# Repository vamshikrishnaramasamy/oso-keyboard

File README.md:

# OSO Keyboard

Demo: https://vamshikrishnaramasamy.github.io/oso-keyboard/

Repository/README: https://github.com/vamshikrishnaramasamy/oso-keyboard

OSO Keyboard is an open-source 75% mechanical keyboard project with a custom
ESP32-S3 programmable PCB target, USB/BLE/Wi-Fi firmware plans, and parametric CAD.

Current design target:

- 82-key 75% ANSI layout with a flush hot-swappable OSO module bay
- Onboard ESP32-S3-WROOM-1U module as the main brain
- USB-C
- 10-contact programmable module dock replacing the Esc/F1 corner
- ESP-IDF/TinyUSB wired firmware target, with BLE/Wi-Fi config planned
- MX hotswap switch footprints
- PCB-mounted stabilizers
- Factory-assembled SMD diodes and ESP32-S3 support parts

The project is intentionally source-driven: edit `hardware/layout/oso75.layout.json`,
then run the generator to refresh firmware layout metadata, CAD key positions,
PCB circuit netlists, and the KiCad starting project.

## Quick Start

```sh
npm run generate
npm run validate
```

Generated CAD lives in `hardware/cad/generated/`. The KiCad project lives in
`hardware/kicad/oso75/`.

## Reviewer File Map

PCB source files:

- KiCad project: `hardware/kicad/oso75/oso75.kicad_pro`
- KiCad schematic: `hardware/kicad/oso75/oso75.kicad_sch`
- KiCad PCB: `hardware/kicad/oso75/oso75.kicad_pcb`
- Order-ready Gerbers/BOM/CPL: `hardware/kicad/oso75/fab/`
- Reviewer BOM with purchase links: `hardware/bom.csv`

CAD source and exports:

- Parametric CAD source: `hardware/cad/build123d/oso75_case.py`
- Full assembly render: `hardware/cad/build123d/oso75_preview_exploded.png`
- Full assembly STEP/GLB: `hardware/cad/build123d/oso75_assembly.step` and
  `hardware/cad/build123d/oso75_assembly.glb`
- Split case top: `hardware/cad/build123d/oso75_case_bezel.step/.stl`
- Split case bottom: `hardware/cad/build123d/oso75_case_bottom.step/.stl`
- Switch plate: `hardware/cad/build123d/oso75_plate.step/.stl`
- Module bay cover: `hardware/cad/build123d/oso75_bay_cover.step/.stl`

## Status

This is the first hardware bring-up pass. The layout, firmware skeleton, CAD
plate/case model, ESP32-S3 pin plan, PCB circuit netlists, and KiCad board
starting point are in place.

2026-06-10: a full orientation audit against the proven annovax75 reference
found the PCB was **physically mirrored** (rows y-inverted: a built board would
have had `~` on the right and Enter on the left). The board was y-flipped
(placements mirrored, every footprint rotated 180°, diodes re-seated at the
x-mirrored offset about their switch) and re-routed from scratch. KiCad 10.0.3
reports 0 DRC errors and 0 unconnected items; drill files reconcile exactly.
The CAD model was already correct and is byte-identical across the fix.

**Order only `hardware/kicad/oso75/fab/oso75_order_ready_v2_gerbers.zip`** (plus
`oso75_order_ready_v2_pos.csv` and the BOM CSVs). Anything prefixed
`STALE-MIRRORED-DO-NOT-ORDER-` is the mirrored board and must not be ordered.
See `hardware/kicad/oso75/fab/README_ORDER_READY.md`.

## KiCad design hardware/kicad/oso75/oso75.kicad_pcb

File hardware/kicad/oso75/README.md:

# OSO75 KiCad Project

Generated from `hardware/layout/oso75.layout.json` and the PCB circuit netlists,
then hand-finished for fabrication. **Do not re-run `scripts/generate-kicad.mjs`
over this board** - it would clobber the routing and the real footprints below.

Open `oso75.kicad_pro` in KiCad 10. The board contains:

- 82 Kailh MX hotswap switch footprints (cloned from the proven annovax75
  reference board: 3.05 mm plated contact holes, 4.0 mm center / 1.75 mm
  fixation NPTH, F.Cu SMD socket pads); Esc and F1 are replaced by the module bay
- 82 SOD-123 diode footprints, 6 x 16 COL2ROW matrix
- ESP32-S3-WROOM-1U-N16 module with native USB and an external IPEX/u.FL
  antenna connector. Do not substitute N16R8/R16V/Octal-PSRAM variants;
  GPIO35/GPIO36/GPIO37 are used by the key matrix.
- USB-C receptacle `Connector_USB:USB_C_Receptacle_HRO_TYPE-C-31-M-12` (J1)
  from the official KiCad library, shield pads solid-connected to GND
- Cherry PCB-mount stabilizer holes (3.048 / 3.988 mm NPTH) for Backspace,
  Enter, LShift (2u wires) and Space (6.25u)
- Flush top-left J3 OSO module bay with 10 contacts and two retention holes.
  Rev A is power-off swappable only; do not live-swap powered modules.
- F1 fused 5 V module rail, R10 module-present pullup, LDO, CC pulldowns,
  USB series resistors, boot/reset, strapping support
- Board outline 337.088 mm x 150.063 mm; GND pours on both copper layers
  with stitching vias

## Status: y-flipped, re-routed, DRC error-clean, ready for prototype fab review

2026-06-10 (evening): **the board was physically mirrored** - all previous
passes (including the Oracle audit) had the rows y-inverted relative to the
proven annovax75 convention, so a built board would have had `~` on the right
and Enter on the left. Fixed by mirroring every footprint placement about the
horizontal centerline (y -> 150.063 - y, each part rotated 180 deg so
y-asymmetric features land correctly; parts are physical and cannot be
mirrored), repositioning each diode at the x-mirrored offset about its own
switch (restores the proven pad clearances), and re-routing from scratch.
The KiCad canvas now reads like a normal keyboard: USB/ESP32 band and the
J3 bay at the top-left, F-row beneath, space row at the bottom.
Current package: `fab/oso75_order_ready_v2_gerbers.zip`; everything prefixed
`STALE-MIRRORED-DO-NOT-ORDER-` is the mirrored board and must not be ordered.

- Oracle review found blocking electrical issues in the previous pass; those
  are fixed in the checked-in board.
- U1 is locked to ESP32-S3-WROOM-1U-N16. Do not substitute N16R8/R16V or other
  Octal-PSRAM ESP32-S3 variants because GPIO35/GPIO36/GPIO37 are matrix columns.
- U3 is wired as:
  pin 1 VIN=VBUS, pin 2 GND, pin 3 EN=VBUS, pin 4 NC, pin 5 VOUT=+3V3.
- Added GND stitching vias to clear isolated F.Cu pour islands created by the
  regulator-area reroute.
- KiCad 10.0.3 DRC after the y-flip and re-route: 0 errors, 0 unconnected
  items, 187 library-lookup warnings only (`drc-yflip-12.json`).
- Current fab package: `fab/oso75_order_ready_v2_gerbers.zip` with
  `oso75_order_ready_v2_pos.csv`. Upload after a final Gerber-viewer check.
- All prior fab packages are the mirrored board and must not be ordered.
- Drill sanity-checked: 164x 3.05 PTH switch contacts, 164x 1.75 NPTH
  fixation, 82x 4.0 NPTH centers, 8x 3.048 + 8x 3.988 NPTH stab holes
- 2-layer, 1.6 mm FR-4, 1 oz; min track/clearance 0.2 mm, vias 0.6/0.3 mm
- Copper-to-edge clearance is set to 0.35 mm (JLCPCB/PCBWay accept >= 0.3)
  because the USB corridor cannot satisfy 0.5 mm
- J3 is exposed ENIG contact copper only: no paste, no BOM line, and no pick
  and place entry. Removable modules must provide the spring/contact side.

## How it was routed

Full-board autoroute with freerouting v2.2.4 (`tools/freerouting/freerouting.jar`):
strip all tracks, `ExportSpecctraDSN` -> `oso75_clean.dsn`, route, import
`oso75.ses`, refill zones (`post_route.py`), widen power nets where clearance
allows (`widen_power.py`), then DRC to zero. Two stubborn matrix links and the
post-layout-fix stitches were routed by the local grid-A* scripts
(`route_two.py`, `route_col9_astar.py`, `route_missing.py`); GND pour islands
got stitching vias (`stitch_islands.py`).

Gotchas discovered (kept for the next pass):

- freerouting v2.2.4 hangs at "Opening..." if the DSN contains existing
  wiring - always strip tracks and route from scratch. It can also hang
  *after* "session completed" without writing the .ses; kill and re-run.
- `pcbnew.LoadBoard` returns None unless the path ends in `.kicad_pcb`.
- The original generator switch footprints were placeholders with no real
  MX contact pads - they were replaced wholesale (see `move_sw72.py`,
  git history) and PrtSc was moved to the nav column (layout bug, 0.75u
  keycap overlap with F12).

2026-06-10: the rear electronics band was shrunk from 45 mm to 22 mm deep
(board 173.063 -> 150.063 mm tall, `rearElectronicsHeight` 36 -> 13 in the
generator/validator). U1 is now the external-antenna WROOM-1U-N16 module, so
there is no PCB antenna area on the keyboard PCB. USB/LDO/passives were
repacked, stabilizer footprints were added, and the board was fully re-routed.

Pre-route and pre-move backups: `oso75.kicad_pcb.bak`,
`oso75.kicad_pcb.pre-sw72`, `oso75.kicad_pcb.pre-shrink` (173 mm board).

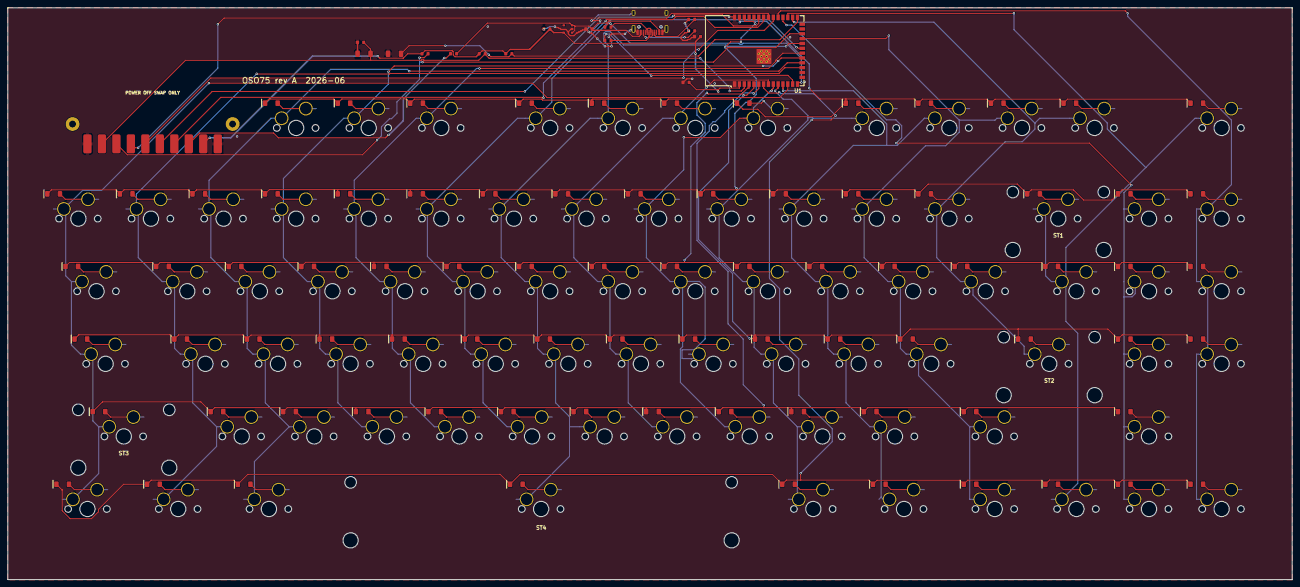
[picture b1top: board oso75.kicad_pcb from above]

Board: 2 copper layers, 337.1 x 150.1 mm, 187 parts (0 on the bottom side), 121 nets.

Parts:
C1, C2: 10uF; C_0603
C3, C4: 100nF; C_0603
C_EN: 1uF; C_0603
D1, D2, D3, D4, D5, D6, D7, D8, D9, D10, D11, D12, D13, D14, D15, D16, D17, D18, D19, D20, D21, D22, D23, D24, D25, D26, D27, D28, D29, D30, D31, D32, D33, D34, D35, D36, D37, D38, D39, D40, D41, D42, D43, D44, D45, D46, D47, D48, D49, D50, D51, D52, D53, D54, D55, D56, D57, D58, D59, D60, D61, D62, D63, D64, D65, D66, D67, D68, D69, D70, D71, D72, D73, D74, D75, D76, D77, D78, D79, D80, D81, D82: 1N4148W; D_SOD-123_Keyboard
F1: 0603L050SLYR; Polyfuse_0603
J1: USB_C_HRO_TYPE-C-31-M-12; USB_C_Receptacle_HRO_TYPE-C-31-M-12
J3: Exposed_OSO_Bay_Pads_DNP; OSO_Module_Bay_10
R1, R2: 5.1k; R_0603
R3, R4: 27R; R_0603
R5, R6, R10: 10k; R_0603
ST1, ST2, ST3: Stabilizer_Cherry_MX_2.00u
ST4: Stabilizer_Cherry_MX_6.25u
SW1, SW2, SW3, SW4, SW5, SW6, SW7, SW8, SW9, SW10, SW11, SW12, SW13, SW14, SW15, SW16, SW17, SW18, SW19, SW20, SW21, SW22, SW23, SW24, SW25, SW26, SW27, SW28, SW29, SW30, SW31, SW32, SW33, SW34, SW35, SW36, SW37, SW38, SW39, SW40, SW41, SW42, SW43, SW44, SW45, SW46, SW47, SW48, SW49, SW50, SW51, SW52, SW53, SW54, SW55, SW56, SW57, SW58, SW59, SW60, SW61, SW62, SW63, SW64, SW65, SW66, SW67, SW68, SW69, SW70, SW71, SW72, SW73, SW74, SW75, SW76, SW77, SW78, SW79, SW80, SW81, SW82: MX_Hotswap; SW_Hotswap_Kailh_MX_Plated_1.00u_With_Switch
SW_BOOT: BOOT; SW_Tactile_4x3
SW_RESET: RESET; SW_Tactile_4x3
U1: ESP32-S3-WROOM-1U-N16
U3: AP2112K-3.3; SOT-23-5_LDO

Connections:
+3V3: C2.1, C3.1, C4.1, J3.2, R5.2, R6.2, R10.2, U1.2, U3.5
BOOT_IO0: R6.1, SW_BOOT.1, U1.27
COL0: SW12.1, SW26.1, SW40.1, SW53.1, SW65.1, U1.12
COL1: SW13.1, SW27.1, SW41.1, SW54.1, SW66.1, U1.17
COL2: SW1.1, SW14.1, SW28.1, SW42.1, SW55.1, SW67.1, U1.18
COL3: SW2.1, SW15.1, SW29.1, SW43.1, SW56.1, U1.19
COL4: SW3.1, SW16.1, SW30.1, SW44.1, SW57.1, U1.20
COL5: SW4.1, SW17.1, SW31.1, SW45.1, SW58.1, U1.21
COL6: SW5.1, SW18.1, SW32.1, SW46.1, SW59.1, SW68.1, U1.22
COL7: SW6.1, SW19.1, SW33.1, SW47.1, SW60.1, U1.8
COL8: SW7.1, SW20.1, SW34.1, SW48.1, SW61.1, U1.9
COL9: SW8.1, SW21.1, SW35.1, SW49.1, SW62.1, SW69.1, U1.10
COL10: SW9.1, SW22.1, SW36.1, SW50.1, SW63.1, SW70.1, U1.11
COL11: SW10.1, SW23.1, SW37.1, SW51.1, SW64.1, SW71.1, U1.23
COL12: SW11.1, SW24.1, SW38.1, SW52.1, U1.28
COL13: SW25.1, SW39.1, SW72.1, SW80.1, U1.29
COL14: SW73.1, SW75.1, SW77.1, SW79.1, SW81.1, U1.30
COL15: SW74.1, SW76.1, SW78.1, SW82.1, U1.31
D1_A: D1.2, SW1.2
D2_A: D2.2, SW2.2
D3_A: D3.2, SW3.2
D4_A: D4.2, SW4.2
D5_A: D5.2, SW5.2
D6_A: D6.2, SW6.2
D7_A: D7.2, SW7.2
D8_A: D8.2, SW8.2
D9_A: D9.2, SW9.2
D10_A: D10.2, SW10.2
D11_A: D11.2, SW11.2
D12_A: D12.2, SW12.2
D13_A: D13.2, SW13.2
D14_A: D14.2, SW14.2
D15_A: D15.2, SW15.2
D16_A: D16.2, SW16.2
D17_A: D17.2, SW17.2
D18_A: D18.2, SW18.2
D19_A: D19.2, SW19.2
D20_A: D20.2, SW20.2
D21_A: D21.2, SW21.2
D22_A: D22.2, SW22.2
D23_A: D23.2, SW23.2
D24_A: D24.2, SW24.2
D25_A: D25.2, SW25.2
D26_A: D26.2, SW26.2
D27_A: D27.2, SW27.2
D28_A: D28.2, SW28.2
D29_A: D29.2, SW29.2
D30_A: D30.2, SW30.2
D31_A: D31.2, SW31.2
D32_A: D32.2, SW32.2
D33_A: D33.2, SW33.2
D34_A: D34.2, SW34.2
D35_A: D35.2, SW35.2
D36_A: D36.2, SW36.2
D37_A: D37.2, SW37.2
D38_A: D38.2, SW38.2
D39_A: D39.2, SW39.2
D40_A: D40.2, SW40.2
D41_A: D41.2, SW41.2
D42_A: D42.2, SW42.2
D43_A: D43.2, SW43.2
D44_A: D44.2, SW44.2
D45_A: D45.2, SW45.2
D46_A: D46.2, SW46.2
D47_A: D47.2, SW47.2
D48_A: D48.2, SW48.2
D49_A: D49.2, SW49.2
D50_A: D50.2, SW50.2
D51_A: D51.2, SW51.2
D52_A: D52.2, SW52.2
D53_A: D53.2, SW53.2
D54_A: D54.2, SW54.2
D55_A: D55.2, SW55.2
D56_A: D56.2, SW56.2
D57_A: D57.2, SW57.2
D58_A: D58.2, SW58.2
D59_A: D59.2, SW59.2
D60_A: D60.2, SW60.2
D61_A: D61.2, SW61.2
D62_A: D62.2, SW62.2
D63_A: D63.2, SW63.2
D64_A: D64.2, SW64.2
D65_A: D65.2, SW65.2
D66_A: D66.2, SW66.2
D67_A: D67.2, SW67.2
D68_A: D68.2, SW68.2
D69_A: D69.2, SW69.2
D70_A: D70.2, SW70.2
D71_A: D71.2, SW71.2
D72_A: D72.2, SW72.2
D73_A: D73.2, SW73.2
D74_A: D74.2, SW74.2
D75_A: D75.2, SW75.2
D76_A: D76.2, SW76.2
D77_A: D77.2, SW77.2
D78_A: D78.2, SW78.2
D79_A: D79.2, SW79.2
D80_A: D80.2, SW80.2
D81_A: D81.2, SW81.2
D82_A: D82.2, SW82.2
ESP_EN: C_EN.1, J3.9, R5.1, SW_RESET.1, U1.3
GND: C1.2, C2.2, C3.2, C4.2, C_EN.2, J1.A1, J1.A12, J1.B1, J1.B12, J1.SH, J3.1, J3.10, R1.2, R2.2, SW_BOOT.2, SW_RESET.2, U1.1, U1.40, U1.41, U3.2
I2C_SCL: J3.5, U1.35
I2C_SDA: J3.4, U1.34
MOD_A: J3.6, U1.32
MOD_B: J3.7, U1.33
MOD_INT: J3.8, R10.1, U1.24
ROW0: D1.1, D2.1, D3.1, D4.1, D5.1, D6.1, D7.1, D8.1, D9.1, D10.1, D11.1, D72.1, U1.39
ROW1: D12.1, D13.1, D14.1, D15.1, D16.1, D17.1, D18.1, D19.1, D20.1, D21.1, D22.1, D23.1, D24.1, D25.1, D73.1, D74.1, U1.38
ROW2: D26.1, D27.1, D28.1, D29.1, D30.1, D31.1, D32.1, D33.1, D34.1, D35.1, D36.1, D37.1, D38.1, D39.1, D75.1, D76.1, U1.4
ROW3: D40.1, D41.1, D42.1, D43.1, D44.1, D45.1, D46.1, D47.1, D48.1, D49.1, D50.1, D51.1, D52.1, D77.1, D78.1, U1.5
ROW4: D53.1, D54.1, D55.1, D56.1, D57.1, D58.1, D59.1, D60.1, D61.1, D62.1, D63.1, D64.1, D79.1, U1.6
ROW5: D65.1, D66.1, D67.1, D68.1, D69.1, D70.1, D71.1, D80.1, D81.1, D82.1, U1.7
USB_CC1: J1.A5, R1.1
USB_CC2: J1.B5, R2.1
USB_DM: R4.2, U1.13
USB_DM_CONN: J1.A7, J1.B7, R4.1
USB_DP: R3.2, U1.14
USB_DP_CONN: J1.A6, J1.B6, R3.1
VBUS: C1.1, F1.1, J1.A4, J1.A9, J1.B4, J1.B9, U3.1, U3.3
VBUS_FUSED: F1.2, J3.3

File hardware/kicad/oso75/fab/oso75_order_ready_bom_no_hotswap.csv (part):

Comment,Designator,Footprint,Quantity,MPN/Part,Notes
ESP32-S3-WROOM-1U-N16,U1,RF module with external IPEX antenna,1,ESP32-S3-WROOM-1U-N16,"Main MCU module with native USB, Wi-Fi, BLE, 16 MB flash, and external antenna connector; do not substitute N16R8/R16V/Octal-PSRAM variants"
3.3 V LDO,U3,SOT-23-5,1,AP2112K-3.3TRG1,USB 5 V to 3.3 V
USB-C receptacle,J1,USB-C-16P-SMD,1,HRO TYPE-C-31-M-12,USB 2.0 device port
500mA resettable fuse,F1,0603 PPTC,1,Littelfuse 0603L050SLYR,6 V 500 mA hold resettable fuse for optional module-bay 5 V
Boot tactile switch,SW_BOOT,SMD tactile,1,SKRPACE010,Pull GPIO0 low for ROM download mode
Reset tactile switch,SW_RESET,SMD tactile,1,SKRPACE010,Pull EN low
5.1k,R1,0603,1,generic,USB-C CC1 pulldown
5.1k,R2,0603,1,generic,USB-C CC2 pulldown
27R,R3,0603,1,generic,USB D+ series
27R,R4,0603,1,generic,USB D- series
10k,R5,0603,1,generic,ESP_EN pullup
10k,R6,0603,1,generic,GPIO0 boot pullup
10k,R10,0603,1,generic,Module present/interrupt pullup
10uF 10V,C1,0603,1,generic X5R/X7R,LDO input; footprint is 0603 only
10uF 10V,C2,0603,1,generic X5R/X7R,LDO output; footprint is 0603 only
100nF,"C3,C4",0603,2,generic X7R,ESP32 local decoupling
1uF,C_EN,0603,1,generic X5R/X7R,ESP_EN reset delay capacitor
1N4148W,D1,SOD-123,1,1N4148W,F2 anti-ghosting diode; pad 1/cathode band faces ROW net
1N4148W,D2,SOD-123,1,1N4148W,F3 anti-ghosting diode; pad 1/cathode band faces ROW net
1N4148W,D3,SOD-123,1,1N4148W,F4 anti-ghosting diode; pad 1/cathode band faces ROW net
1N4148W,D4,SOD-123,1,1N4148W,F5 anti-ghosting diode; pad 1/cathode band faces ROW net
1N4148W,D5,SOD-123,1,1N4148W,F6 anti-ghosting diode; pad 1/cathode band faces ROW net
1N4148W,D6,SOD-123,1,1N4148W,F7 anti-ghosting diode; pad 1/cathode band faces ROW net
1N4148W,D7,SOD-123,1,1N4148W,F8 anti-ghosting diode; pad 1/cathode band faces ROW net
1N4148W,D8,SOD-123,1,1N4148W,F9 anti-ghosting diode; pad 1/cathode band faces ROW net
1N4148W,D9,SOD-123,1,1N4148W,F10 anti-ghosting diode; pad 1/cathode band faces ROW net
1N4148W,D10,SOD-123,1,1N4148W,F11 anti-ghosting diode; pad 1/cathode band faces ROW net
1N4148W,D11,SOD-123,1,1N4148W,F12 anti-ghosting diode; pad 1/cathode band faces ROW net
1N4148W,D12,SOD-123,1,1N4148W,` anti-ghosting diode; pad 1/cathode band faces ROW net
1N4148W,D13,SOD-123,1,1N4148W,1 anti-ghosting diode; pad 1/cathode band faces ROW net
1N4148W,D14,SOD-123,1,1N4148W,2 anti-ghosting diode; pad 1/cathode band faces ROW net
1N4148W,D15,SOD-123,1,1N4148W,3 anti-ghosting diode; pad 1/cathode band faces ROW net
1N4148W,D16,SOD-123,1,1N4148W,4 anti-ghosting diode; pad 1/cathode band faces ROW net
1N4148W,D17,SOD-123,1,1N4148W,5 anti-ghosting diode; pad 1/cathode band faces ROW net
1N4148W,D18,SOD-123,1,1N4148W,6 anti-ghosting diode; pad 1/cathode band faces ROW net
1N4148W,D19,SOD-123,1,1N4148W,7 anti-ghosting diode; pad 1/cathode band faces ROW net
1N4148W,D20,SOD-123,1,1N4148W,8 anti-ghosting diode; pad 1/cathode band faces ROW net
1N4148W,D21,SOD-123,1,1N4148W,9 anti-ghosting diode; pad 1/cathode band faces ROW net
1N4148W,D22,SOD-123,1,1N4148W,0 anti-ghosting diode; pad 1/cathode band faces ROW net
1N4148W,D23,SOD-123,1,1N4148W,- anti-ghosting diode; pad 1/cathode band faces ROW net
1N4148W,D24,SOD-123,1,1N4148W,= anti-ghosting diode; pad 1/cathode band faces ROW net
1N4148W,D25,SOD-123,1,1N4148W,Backspace anti-ghosting diode; pad 1/cathode band faces ROW net
1N4148W,D26,SOD-123,1,1N4148W,Tab anti-ghosting diode; pad 1/cathode band faces ROW net
1N4148W,D27,SOD-123,1,1N4148W,Q anti-ghosting diode; pad 1/cathode band faces ROW net
1N4148W,D28,SOD-123,1,1N4148W,W anti-ghosting diode; pad 1/cathode band faces ROW net
1N4148W,D29,SOD-123,1,1N4148W,E anti-ghosting diode; pad 1/cathode band faces ROW net
1N4148W,D30,SOD-123,1,1N4148W,R anti-ghosting diode; pad 1/cathode band faces ROW net
1N4148W,D31,SOD-123,1,1N4148W,T anti-ghosting diode; pad 1/cathode band faces ROW net
1N4148W,D32,SOD-123,1,1N4148W,Y anti-ghosting diode; pad 1/cathode band faces ROW net
1N4148W,D33,SOD-123,1,1N4148W,U anti-ghosting diode; pad 1/cathode band faces ROW net
1N4148W,D34,SOD-123,1,1N4148W,I anti-ghosting diode; pad 1/cathode band faces ROW net
1N4148W,D35,SOD-123,1,1N4148W,O anti-ghosting diode; pad 1/cathode band faces ROW net
1N4148W,D36,SOD-123,1,1N4148W,P anti-ghosting diode; pad 1/cathode band faces ROW net
1N4148W,D37,SOD-123,1,1N4148W,[ anti-ghosting diode; pad 1/cathode band faces ROW net
1N4148W,D38,SOD-123,1,1N4148W,] anti-ghosting diode; pad 1/cathode band faces ROW net
1N4148W,D39,SOD-123,1,1N4148W,\ anti-ghosting diode; pad 1/cathode band faces ROW net
1N4148W,D40,SOD-123,1,1N4148W,Caps anti-ghosting diode; pad 1/cathode band faces ROW net
1N4148W,D41,SOD-123,1,1N4148W,A anti-ghosting diode; pad 1/cathode band faces ROW net
1N4148W,D42,SOD-123,1,1N4148W,S anti-ghosting diode; pad 1/cathode band faces ROW net
1N4148W,D43,SOD-123,1,1N4148W,D anti-ghosting diode; pad 1/cathode band faces ROW net
1N4148W,D44,SOD-123,1,1N4148W,F anti-ghosting diode; pad 1/cathode band faces ROW net
1N4148W,D45,SOD-123,1,1N4148W,G anti-ghosting diode; pad 1/cathode band faces ROW net
1N4148W,D46,SOD-123,1,1N4148W,H anti-ghosting diode; pad 1/cathode band faces ROW net
1N4148W,D47,SOD-123,1,1N4148W,J anti-ghosting diode; pad 1/cathode band faces ROW net
1N4148W,D48,SOD-123,1,1N4148W,K anti-ghosting diode; pad 1/cathode band faces ROW net
1N4148W,D49,SOD-123,1,1N4148W,L anti-ghosting diode; pad 1/cathode band faces ROW net
1N4148W,D50,SOD-123,1,1N4148W,; anti-ghosting diode; pad 1/cathode band faces ROW net
1N4148W,D51,SOD-123,1,1N4148W,' anti-ghosting diode; pad 1/cathode band faces ROW net
1N4148W,D52,SOD-123,1,1N4148W,Enter anti-ghosting diode; pad 1/cathode band faces ROW net
1N4148W,D53,SOD-123,1,1N4148W,LShift anti-ghosting diode; pad 1/cathode band faces ROW net
1N4148W,D54,SOD-123,1,1N4148W,Z anti-ghosting diode; pad 1/cathode band faces ROW net
1N4148W,D55,SOD-123,1,1N4148W,X anti-ghosting diode; pad 1/cathode band faces ROW net
1N4148W,D56,SOD-123,1,1N4148W,C anti-ghosting diode; pad 1/cathode band faces ROW net
1N4148W,D57,SOD-123,1,1N4148W,V anti-ghosting diode; pad 1/cathode band faces ROW net
1N4148W,D58,SOD-123,1,1N4148W,B anti-ghosting diode; pad 1/cathode band faces ROW net
1N4148W,D59,SOD-123,1,1N4148W,N anti-ghosting diode; pad 1/cathode band faces ROW net
1N4148W,D60,SOD-123,1,1N4148W,M anti-ghosting diode; pad 1/cathode band faces ROW net
1N4148W,D61,SOD-123,1,1N4148W,", anti-ghosting diode; pad 1/cathode band faces ROW net"
1N4148W,D62,SOD-123,1,1N4148W,. anti-ghosting diode; pad 1/cathode band faces ROW net
1N4148W,D63,SOD-123,1,1N4148W,/ anti-ghosting diode; pad 1/cathode band faces ROW net
1N4148W,D64,SOD-123,1,1N4148W,RShift anti-ghosting diode; pad 1/cathode band faces ROW net
1N4148W,D65,SOD-123,1,1N4148W,LCtrl anti-ghosting diode; pad 1/cathode band faces ROW net
1N4148W,D66,SOD-123,1,1N4148W,LGUI anti-ghosting diode; pad 1/cathode band faces ROW net
1N4148W,D67,SOD-123,1,1N4148W,LAlt anti-ghosting diode; pad 1/cathode band faces ROW net
1N4148W,D68,SOD-123,1,1N4148W,Space anti-ghosting diode; pad 1/cathode band faces ROW net
1N4148W,D69,SOD-123,1,1N4148W,RAlt anti-ghosting diode; pad 1/cathode band faces ROW net
1N4148W,D70,SOD-123,1,1N4148W,Fn anti-ghosting diode; pad 1/cathode band faces ROW net
1N4148W,D71,SOD-123,1,1N4148W,RCtrl anti-ghosting diode; pad 1/cathode band faces ROW net
1N4148W,D72,SOD-123,1,1N4148W,PrtSc anti-ghosting diode; pad 1/cathode band faces ROW net
1N4148W,D73,SOD-123,1,1N4148W,Ins anti-ghosting diode; pad 1/cathode band faces ROW net
1N4148W,D74,SOD-123,1,1N4148W,Home anti-ghosting diode; pad 1/cathode band faces ROW net
1N4148W,D75,SOD-123,1,1N4148W,PgUp anti-ghosting diode; pad 1/cathode band faces ROW net
1N4148W,D76,SOD-123,1,1N4148W,Del anti-ghosting diode; pad 1/cathode band faces ROW net
1N4148W,D77,SOD-123,1,1N4148W,End anti-ghosting diode; pad 1/cathode band faces ROW net
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
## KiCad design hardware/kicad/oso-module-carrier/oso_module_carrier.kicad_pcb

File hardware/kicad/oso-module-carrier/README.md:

# OSO Module Carrier (XIAO + Qwiic)

The first OSO module: a 54 x 25 mm carrier for the OSO75 bay that makes
the whole Qwiic/STEMMA-QT ecosystem — and optionally a whole second
ESP32 — pluggable into the keyboard. DRC-clean, fully routed
(`fab/oso_module_carrier_gerbers.zip`).

Two personalities on one PCB:

| Mode | Fit | JP1/JP2 (I2C bridge) | JP3 (5 V) |
|---|---|---|---|
| Dumb Qwiic adapter (default) | no XIAO | bridged (factory default) | open |
| Smart module | XIAO ESP32-S3 in U2/U3 | **cut** | close to power XIAO from bay |

- **Dumb mode**: the keyboard's ESP32-S3 drives any Qwiic device plugged
  into J1/J2 over the bay I2C (GPIO41/42). Zero firmware on the module.
- **Smart mode**: the XIAO owns the Qwiic (device) bus on D2/D3 and talks
  to the keyboard over the bay (link) bus on D4/D5 as an I2C peripheral;
  MOD_INT (keyboard GPIO47 / XIAO D1) is the attention line. The XIAO's
  USB-C faces up through the bay for reflashing. MOD_A/B also land on
  D0/D6 as spare link lines.

## Parts

| Ref | Part |
|---|---|
| MOD1 | ten 2.2 x 5.0 bottom pads (3.8 mm pitch) at the keyboard J3 pad positions — solder **Mill-Max 0965-0-15-20-80-14-11-0** SMT spring pins here (2.79 mm extended, ~2.5 mm at rated mid-stroke, 2 A) |
| U2/U3 | 1x7 2.54 mm SMD socket strips (XIAO ESP32-S3 seat) |
| J1/J2 | JST SH 4-pin (SM04B-SRSS-TB) = Qwiic / STEMMA-QT |
| J4 | 1x4 pin header: 3V3 / GND / MOD_A / MOD_B (encoders, raw GPIO) |
| JP1/JP2 | solder jumpers: bay I2C <-> Qwiic bus (bridged by default) |
| JP3 | solder jumper: bay fused 5 V -> XIAO 5 V pin (open by default) |
| C1/C2 | 100 nF + 10 uF 0603 on 3V3 |
| R1 | 10 k 0603, MOD_INT -> GND (module-present strap) |

Retention: Ø3.6 NPTH at ±21 mm, matching the bay's holes. ESP_EN from
the bay lands on contact 9 (unrouted on the carrier by design).

**Polarization**: the back-left corner has a 5 mm chamfer and the case
plate's bay opening a matching 2.2 mm corner key — the module physically
cannot be inserted 180° rotated (which would land 5 V/EN on the I2C
contacts). Cross-board mating is machine-verified: every contact pad's
position, size and net function is checked against the keyboard's J3 by
`verify_carrier.py` (87 checks).

## Regenerating

`generate_carrier.py` (run under KiCad's bundled python) rebuilds
placement/nets/zones from scratch; route with
`java -jar tools/freerouting/freerouting.jar -de oso_module_carrier.dsn
-do oso_module_carrier.ses -mp 10` and apply with `import_ses.py`
(pcbnew's own SES import returns False headless on this machine).
Note: regenerating discards the routed tracks and the hand-placed GND
stitch at J2 — re-run the route + import steps after.

See `docs/oso-module-spec.md` for the full bay interface contract.

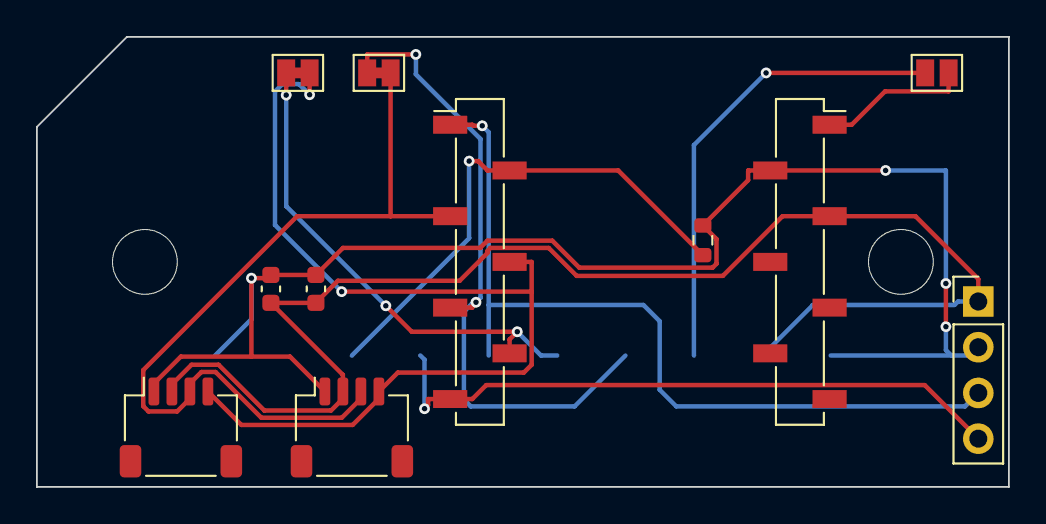
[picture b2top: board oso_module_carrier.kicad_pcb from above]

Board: 2 copper layers, 54.0 x 25.0 mm, 12 parts (0 on the bottom side), 11 nets.

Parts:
C1, C2: C_0603_1608Metric
J1, J2: JST_SH_SM04B-SRSS-TB_1x04-1MP_P1.00mm_Horizontal
J4: PinHeader_1x04_P2.54mm_Vertical
JP1, JP2: SolderJumper-2_P1.3mm_Bridged_Pad1.0x1.5mm
JP3: SolderJumper-2_P1.3mm_Open_Pad1.0x1.5mm
MOD1: OSO_BAY_CONTACTS
R1: R_0603_1608Metric
U2: PinSocket_1x07_P2.54mm_Vertical_SMD_Pin1Left
U3: PinSocket_1x07_P2.54mm_Vertical_SMD_Pin1Right

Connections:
+3V3: C1.1, C2.1, J1.2, J2.2, J4.1, MOD1.2, U3.3
GND: C1.2, C2.2, J1.1, J2.1, J4.2, MOD1.1, MOD1.10, R1.2, U3.2
MOD_A: J4.3, MOD1.6, U2.1
MOD_B: J4.4, MOD1.7, U2.7
MOD_INT: MOD1.8, R1.1, U2.2
SCL_BAY: JP2.1, MOD1.5, U2.6
SCL_DEV: J1.4, J2.4, JP2.2, U2.4
SDA_BAY: JP1.1, MOD1.4, U2.5
SDA_DEV: J1.3, J2.3, JP1.2, U2.3
VBUS_FUSED: JP3.1, MOD1.3
XIAO_5V: JP3.2, U3.1

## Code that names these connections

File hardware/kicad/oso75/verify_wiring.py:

"""Electrical verification of oso75.kicad_pcb against the documented wiring:
  - every switch/diode connection in oso75_matrix_netlist.csv
  - every ROW/COL net lands on the correct physical ESP32-S3-WROOM-1U pad
    for the GPIO assigned in qmk keyboard.json
  - J3 module bay pads 1-10 carry the nets from oso75_circuit.md
  - bay signals reach the documented U1 GPIOs (I2C 41/42, MOD_A/B 39/40,
    MOD_INT 47, ESP_EN -> EN)
  - zero unconnected items in the routed board
"""
import csv, json, sys
import pcbnew

ROOT = "/Users/vamshikrishnaramasamy/CodeProjects/OSO Keyboard"
board = pcbnew.LoadBoard(f"{ROOT}/hardware/kicad/oso75/oso75.kicad_pcb")

# ref -> {pad_number: net_name}
pads = {}
for fp in board.GetFootprints():
    ref = fp.GetReference()
    pads.setdefault(ref, {})
    for p in fp.Pads():
        if p.GetNumber():
            pads[ref][p.GetNumber()] = p.GetNetname()

fails = []
ok = 0
def check(cond, msg):
    global ok
    if cond: ok += 1
    else: fails.append(msg)

# ---- 1. switch matrix: every connection in the CSV exists in copper
with open(f"{ROOT}/hardware/pcb/oso75_matrix_netlist.csv") as f:
    rows = list(csv.DictReader(f))
check(len(rows) == 82, f"expected 82 matrix entries, got {len(rows)}")
for r in rows:
    sw, d = pads.get(r["switch_ref"], {}), pads.get(r["diode_ref"], {})
    check(sw.get("1") == r["switch_pin_1"],
          f'{r["switch_ref"]} pad1 = {sw.get("1")} want {r["switch_pin_1"]}')
    check(sw.get("2") == r["switch_pin_2"],
          f'{r["switch_ref"]} pad2 = {sw.get("2")} want {r["switch_pin_2"]}')
    # diode: pad 2 = anode (matrix convention here), pad 1 = cathode
    dnets = set(d.values())
    check(r["diode_anode"] in dnets and r["diode_cathode"] in dnets,
          f'{r["diode_ref"]} nets {dnets} want {r["diode_anode"]}+{r["diode_cathode"]}')

# ---- 2. ROW/COL nets land on the right physical WROOM-1U pad
# ESP32-S3-WROOM-1(U) module pinout: pad number -> GPIO name
WROOM = {3:"EN",4:"GPIO4",5:"GPIO5",6:"GPIO6",7:"GPIO7",8:"GPIO15",9:"GPIO16",
         10:"GPIO17",11:"GPIO18",12:"GPIO8",13:"GPIO19",14:"GPIO20",15:"GPIO3",
         16:"GPIO46",17:"GPIO9",18:"GPIO10",19:"GPIO11",20:"GPIO12",21:"GPIO13",
         22:"GPIO14",23:"GPIO21",24:"GPIO47",25:"GPIO48",26:"GPIO45",27:"GPIO0",
         28:"GPIO35",29:"GPIO36",30:"GPIO37",31:"GPIO38",32:"GPIO39",33:"GPIO40",
         34:"GPIO41",35:"GPIO42",36:"GPIO44",37:"GPIO43",38:"GPIO2",39:"GPIO1"}
gpio_net = {WROOM[int(n)]: net for n, net in pads["U1"].items()
            if n.isdigit() and int(n) in WROOM}

kb = json.load(open(f"{ROOT}/qmk/keyboards/oso/oso75/keyboard.json"))
for i, g in enumerate(kb["matrix_pins"]["rows"]):
    check(gpio_net.get(g) == f"ROW{i}", f"U1 {g} = {gpio_net.get(g)} want ROW{i}")
for i, g in enumerate(kb["matrix_pins"]["cols"]):
    check(gpio_net.get(g) == f"COL{i}", f"U1 {g} = {gpio_net.get(g)} want COL{i}")

# ---- 3. J3 module bay pinout per oso75_circuit.md
J3_EXPECT = {1:"GND",2:"+3V3",3:"VBUS_FUSED",4:"I2C_SDA",5:"I2C_SCL",
             6:"MOD_A",7:"MOD_B",8:"MOD_INT",9:"ESP_EN",10:"GND"}
for n, want in J3_EXPECT.items():
    got = pads.get("J3", {}).get(str(n))
    check(got == want, f"J3 pad {n} = {got} want {want}")

# ---- 4. bay signals reach the documented ESP32 GPIOs
for g, want in [("GPIO41","I2C_SDA"),("GPIO42","I2C_SCL"),("GPIO39","MOD_A"),
                ("GPIO40","MOD_B"),("GPIO47","MOD_INT"),("EN","ESP_EN")]:
    check(gpio_net.get(g) == want, f"U1 {g} = {gpio_net.get(g)} want {want}")
# USB pins must NOT be in the matrix
for g in ("GPIO19", "GPIO20"):
    n = gpio_net.get(g, "")
    check(not n.startswith(("ROW","COL")), f"U1 {g} used by matrix net {n}")

# ---- 5. fully routed: no unconnected items
board.BuildConnectivity()
unrouted = board.GetConnectivity().GetUnconnectedCount(True)
check(unrouted == 0, f"{unrouted} unconnected items remain")

print(f"PASS {ok} checks" if not fails else f"{ok} ok, {len(fails)} FAILED:")
for m in fails:
    print("  FAIL:", m)
sys.exit(1 if fails else 0)

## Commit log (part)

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2026-06-08 Initial OSO keyboard hardware project
2026-06-08 Add GitHub Pages demo link
2026-06-08 Deploy demo to GitHub Pages
2026-06-08 Improve 75 percent CAD model
2026-06-08 Deploy improved CAD demo
2026-06-09 Fix CAD to read as keyboard layout
2026-06-09 Deploy corrected keyboard CAD demo
2026-06-09 Add USB-C receptacle cutout to CAD
2026-06-09 Deploy USB-C CAD update
2026-06-09 Add hot-swappable OSO module bay
2026-06-09 Deploy OSO module bay demo
2026-06-09 Improve CAD viewer rotation controls
2026-06-09 Deploy improved CAD viewer controls
2026-06-09 Move OSO module bay onto compact tab
2026-06-09 Deploy compact OSO module tab
2026-06-09 Make OSO module bay flush with keyboard outline
2026-06-09 Deploy flush OSO module bay
2026-06-09 Update PCB for flush OSO module bay
2026-06-09 Deploy PCB module bay update
